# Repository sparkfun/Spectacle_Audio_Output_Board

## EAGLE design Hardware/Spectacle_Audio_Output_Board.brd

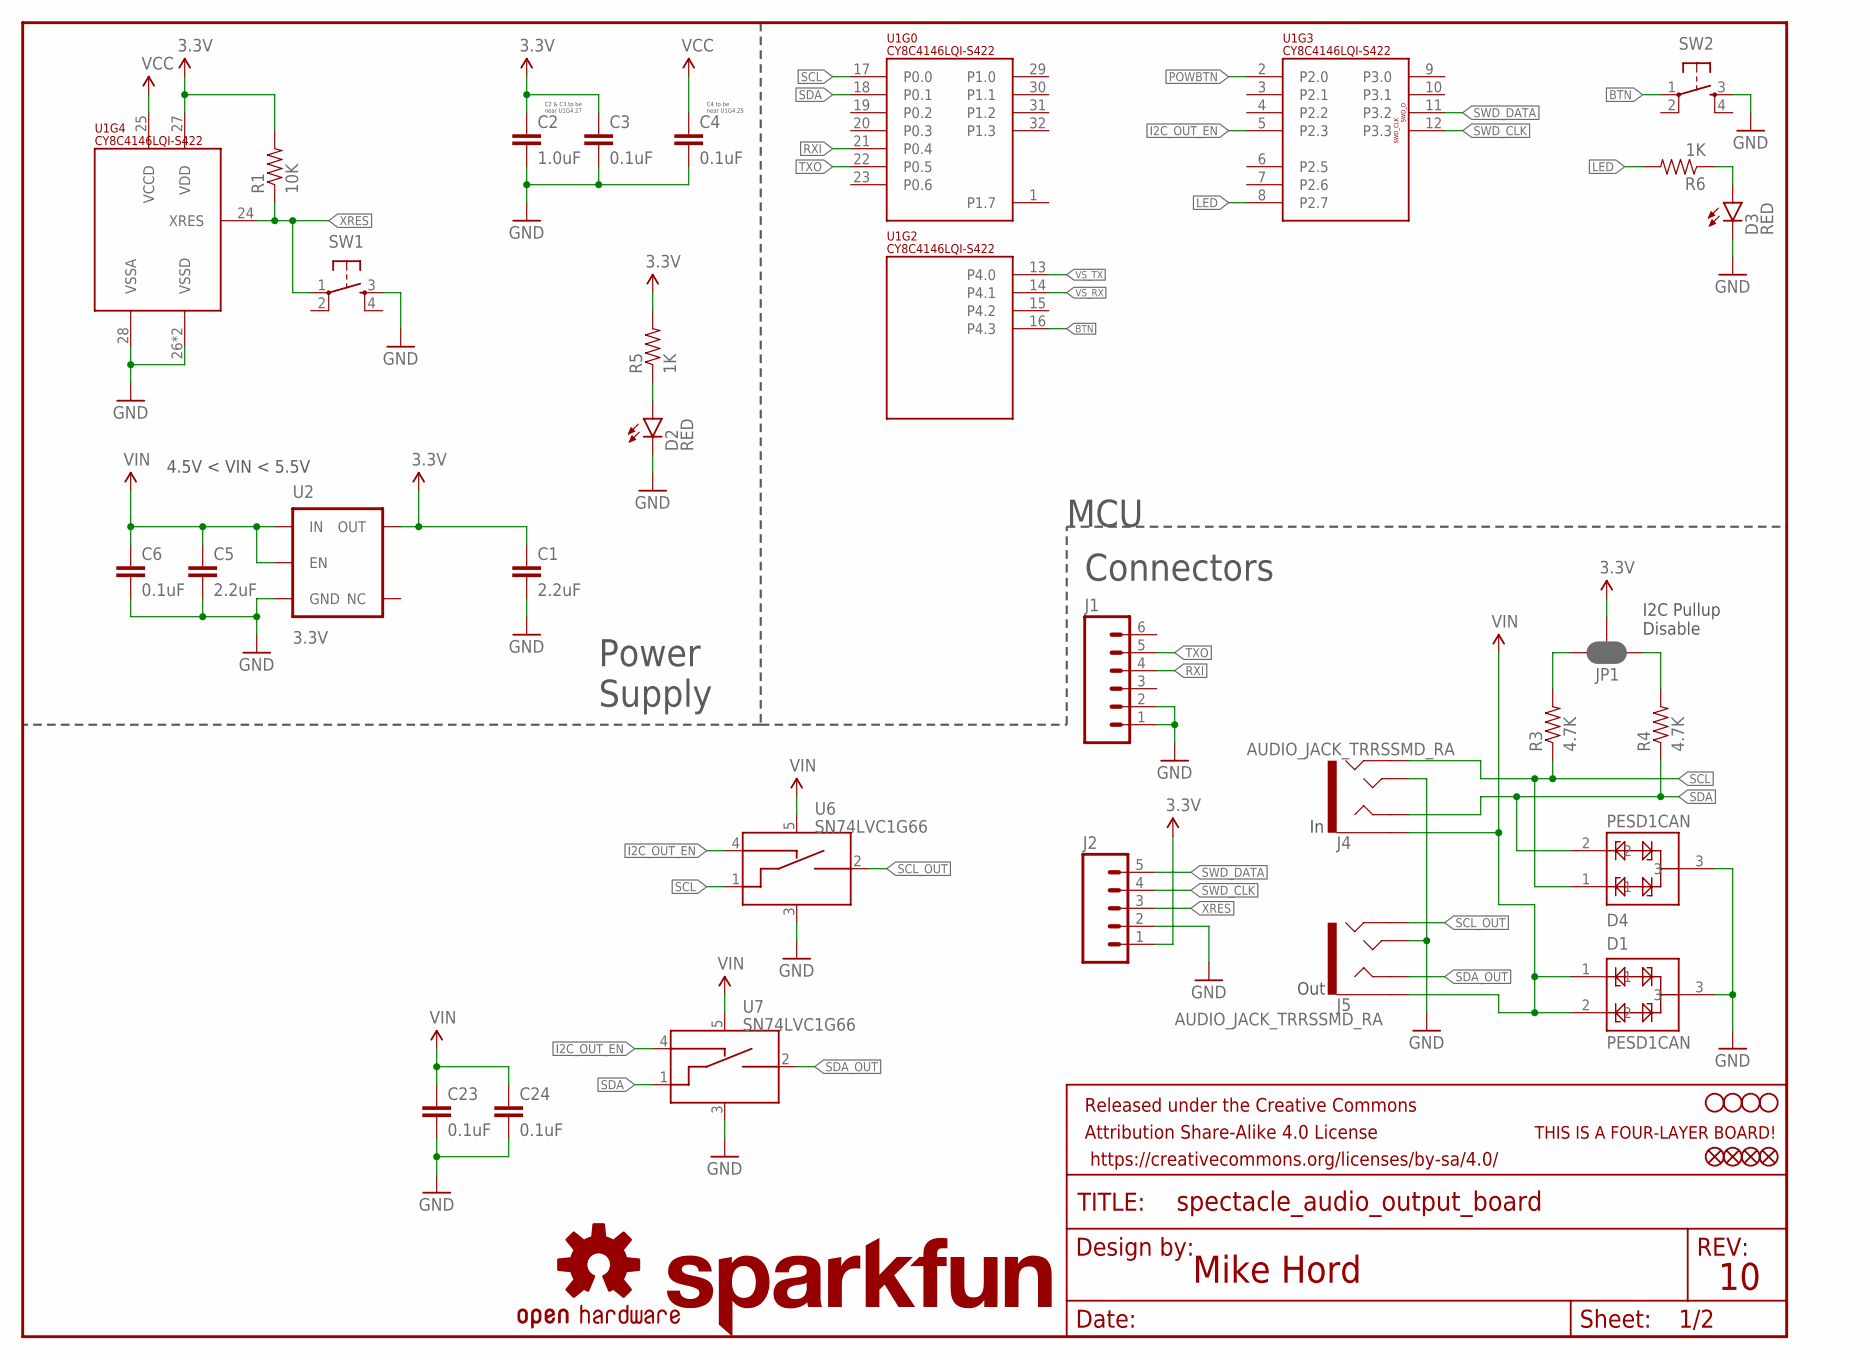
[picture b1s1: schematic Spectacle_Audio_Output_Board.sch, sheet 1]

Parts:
C1, C5: 2.2uF; 0603-CAP
C2: 1.0uF; 0402-CAP
C3, C4, C6, C23, C24: 0.1uF; 0402-CAP
D1, D4: PESD1CAN; SOT23-3
D2, D3: RED; LED-0603
FD5, FD6, FD7, FD8: FIDUCIALUFIDUCIAL; MICRO-FIDUCIAL
FRAME1: FRAME-LETTER; CREATIVE_COMMONS
H1, H2, H3, H4: STAND-OFF
J1: M06NO_SILK_NO_POP; 1X06_NO_SILK
J2: M05NO_SILK; 1X05_NO_SILK
J4, J5: AUDIO_JACK_TRRSSMD_RA; AUDIO_JACK_3.5MM_TRRS_SMD_RA
JP1: JUMPER-PAD-3-NC_BY_PASTE; PAD-JUMPER-3-NC_BY_PASTE_YES_SILK_FULL_BOX
LOGO1: OSHW-LOGOS; OSHW-LOGO-S
LOGO2: SFE_LOGO_NAME.1_INCH; SFE_LOGO_NAME_.1
R1: 10K; 0603-RES
R3, R4: 4.7K; 0603-RES
R5, R6: 1K; 0603-RES
SW1, SW2: SWITCH_SPST_4_PINRECT; TACTILE_SWITCH_SMD_4.6X2.8MM
U1: CY8C4146LQI-S422; QFN-32
U2: 3.3V; SOT23-5
U6, U7: SN74LVC1G66; SOT23-5
U$1: FOUR_LAYER_WARNING

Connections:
3.3V: C1.1, C2.1, C3.1, J2.1, JP1.2, R1.2, R5.2, U1.27 (VDD), U2.5 (OUT); also elsewhere on the board
BTN: SW2.1, U1.16 (P4.3)
GND: C1.2, C2.2, C3.2, C4.2, C5.2, C6.2, C23.2, C24.2, D1.3, D2.C, D3.C, D4.3, J1.1, J1.2, J2.2, J4.TIP, J5.TIP, SW1.3, SW2.3, U1.26 (VSSD), U1.28 (VSSA), U1.EP (VSSD), U2.2 (GND), U6.3 (VSS), U7.3 (VSS); also elsewhere on the board
I2C_OUT_EN: U1.5 (P2.3), U6.4 (CTRL_IN), U7.4 (CTRL_IN)
LED: R6.2, U1.8 (P2.7)
unnamed: JP1.3, R3.2
unnamed: D2.A, R5.1
unnamed: D3.A, R6.1
unnamed: JP1.1, R4.2
POWBTN: U1.2 (P2.0); also elsewhere on the board
RXI: J1.4, U1.21 (P0.4)
SCL: D4.1, J4.RING2, R3.1, U1.17 (P0.0), U6.1 (A_IN)
SCL_OUT: J5.RING2, U6.2 (A_OUT)
SDA: D4.2, J4.RING1, R4.1, U1.18 (P0.1), U7.1 (A_IN)
SDA_OUT: J5.RING1, U7.2 (A_OUT)
SWD_CLK: J2.4, U1.12 (P3.3)
SWD_DATA: J2.5, U1.11 (P3.2)
TXO: J1.5, U1.22 (P0.5)
VCC: C4.1, U1.25 (VCCD)
VIN: C5.1, C6.1, C23.1, C24.1, D1.1, D1.2, J4.EARTH, J5.EARTH, U2.1 (IN), U2.3 (EN), U6.5 (VCC), U7.5 (VCC); also elsewhere on the board
VS_RX: U1.14 (P4.1); also elsewhere on the board
VS_TX: U1.13 (P4.0); also elsewhere on the board
XRES: J2.3, R1.1, SW1.1, U1.24 (XRES)

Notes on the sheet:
C2 & C3 to be near U1G4.27
C4 to be near U1G4.25
Mike Hord
MCU
Connectors
Power Supply
4.5V < VIN < 5.5V
I2C Pullup Disable
Out

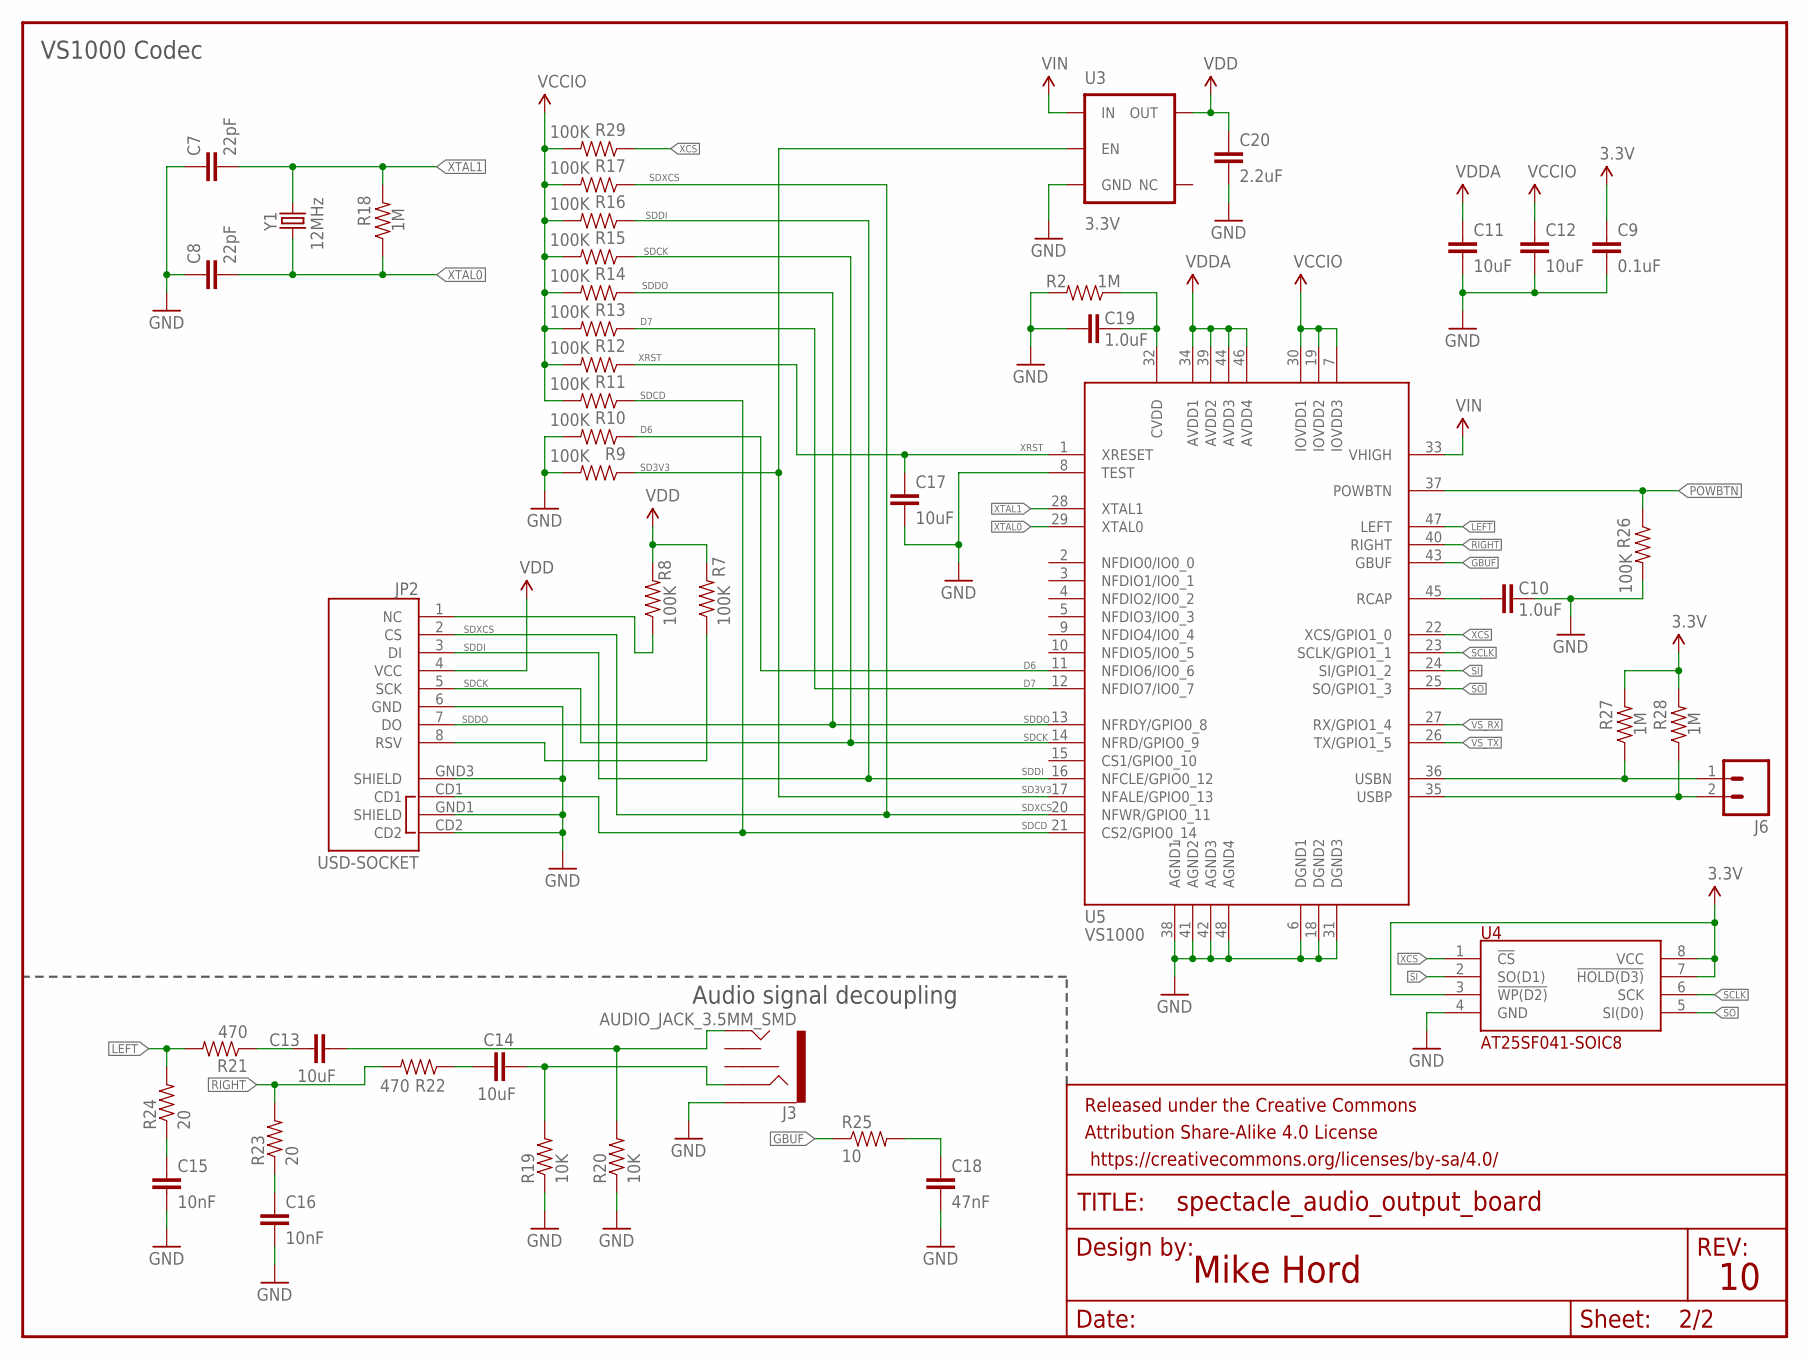
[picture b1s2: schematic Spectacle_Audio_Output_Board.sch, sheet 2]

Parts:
C7, C8: 22pF; 0603-CAP
C9: 0.1uF; 0402-CAP
C10, C19: 1.0uF; 0402-CAP
C11, C12, C13, C14, C17: 10uF; 0603-CAP
C15, C16: 10nF; 0603-CAP
C18: 47nF; 0603-CAP
C20: 2.2uF; 0603-CAP
FRAME2: FRAME-LETTER; CREATIVE_COMMONS
J3: AUDIO_JACK_3.5MM_SMD; AUDIO-JACK-3.5MM-SMD
J6: M021X02_NO_SILK; 1X02_NO_SILK
JP2: USD-SOCKET; MICROSD_1:1
R2, R18, R27, R28: 1M; 0603-RES
R7, R8, R9, R10, R11, R12, R13, R14, R15, R16, R17, R26, R29: 100K; 0402-RES
R19, R20: 10K; 0603-RES
R21, R22: 470; 0603-RES
R23, R24: 20; 0603-RES
R25: 10; 0603-RES
U3: 3.3V; SOT23-5
U4: AT25SF041-SOIC8; SO08
U5: VS1000; LQFP-48
Y1: 12MHz; CRYSTAL-SMD-5X3

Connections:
3.3V: C9.1, R27.2, R28.2, U4.3 (!WP(D2)), U4.7 (!HOLD(D3)), U4.8 (VCC); also elsewhere on the board
D6: R10.1, U5.11 (NFDIO6/IO0_6)
D7: R13.1, U5.12 (NFDIO7/IO0_7)
GBUF: R25.1, U5.43 (GBUF)
GND: C7.1, C8.1, C9.2, C10.2, C11.2, C12.2, C15.2, C16.2, C17.2, C18.2, C19.1, C20.2, J3.SLEEVE, JP2.6 (GND), JP2.CD2, JP2.GND1 (SHIELD), JP2.GND3 (SHIELD), R2.2, R9.2, R10.2, R19.1, R20.1, R26.2, U3.2 (GND), U4.4 (GND), U5.6 (DGND1), U5.8 (TEST), U5.18 (DGND2), U5.31 (DGND3), U5.38 (AGND1), U5.41 (AGND2), U5.42 (AGND3), U5.48 (AGND4); also elsewhere on the board
LEFT: R21.2, R24.2, U5.47 (LEFT)
L_AC: C13.2, J3.TIP, R20.2
unnamed: JP2.1 (NC), R8.1
unnamed: JP2.8 (RSV), R7.1
unnamed: C13.1, R21.1
unnamed: C15.1, R24.1
unnamed: C18.1, R25.2
unnamed: C10.1, U5.45 (RCAP)
unnamed: C19.2, R2.1, U5.32 (CVDD)
unnamed: C14.1, R22.1
unnamed: C16.1, R23.1
POWBTN: R26.1, U5.37 (POWBTN); also elsewhere on the board
RIGHT: R22.2, R23.2, U5.40 (RIGHT)
R_AC: C14.2, J3.RING, R19.2
SCLK: U4.6 (SCK), U5.23 (SCLK/GPIO1_1)
SD3V3: R9.1, U3.3 (EN), U5.17 (NFALE/GPIO0_13)
SDCD: JP2.CD1, R11.1, U5.21 (CS2/GPIO0_14)
SDCK: JP2.5 (SCK), R15.1, U5.14 (NFRD/GPIO0_9)
SDDI: JP2.3 (DI), R16.1, U5.16 (NFCLE/GPIO0_12)
SDDO: JP2.7 (DO), R14.1, U5.13 (NFRDY/GPIO0_8)
SDXCS: JP2.2 (CS), R17.1, U5.20 (NFWR/GPIO0_11)
SI: U4.2 (SO(D1)), U5.24 (SI/GPIO1_2)
SO: U4.5 (SI(D0)), U5.25 (SO/GPIO1_3)
USBN: J6.1, R27.1, U5.36 (USBN)
USBP: J6.2, R28.1, U5.35 (USBP)
VCCIO: C12.1, R11.2, R12.2, R13.2, R14.2, R15.2, R16.2, R17.2, R29.2, U5.7 (IOVDD3), U5.19 (IOVDD2), U5.30 (IOVDD1)
VDD: C20.1, JP2.4 (VCC), R7.2, R8.2, U3.5 (OUT)
VDDA: C11.1, U5.34 (AVDD1), U5.39 (AVDD2), U5.44 (AVDD3), U5.46 (AVDD4)
VIN: U3.1 (IN), U5.33 (VHIGH); also elsewhere on the board
VS_RX: U5.27 (RX/GPIO1_4); also elsewhere on the board
VS_TX: U5.26 (TX/GPIO1_5); also elsewhere on the board
XCS: R29.1, U4.1 (!CS), U5.22 (XCS/GPIO1_0)
XRST: C17.1, R12.1, U5.1 (XRESET)
XTAL0: C8.2, R18.1, U5.29 (XTAL0), Y1.1
XTAL1: C7.2, R18.2, U5.28 (XTAL1), Y1.3 (2)

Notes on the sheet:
Audio signal decoupling
VS1000 Codec
Mike Hord

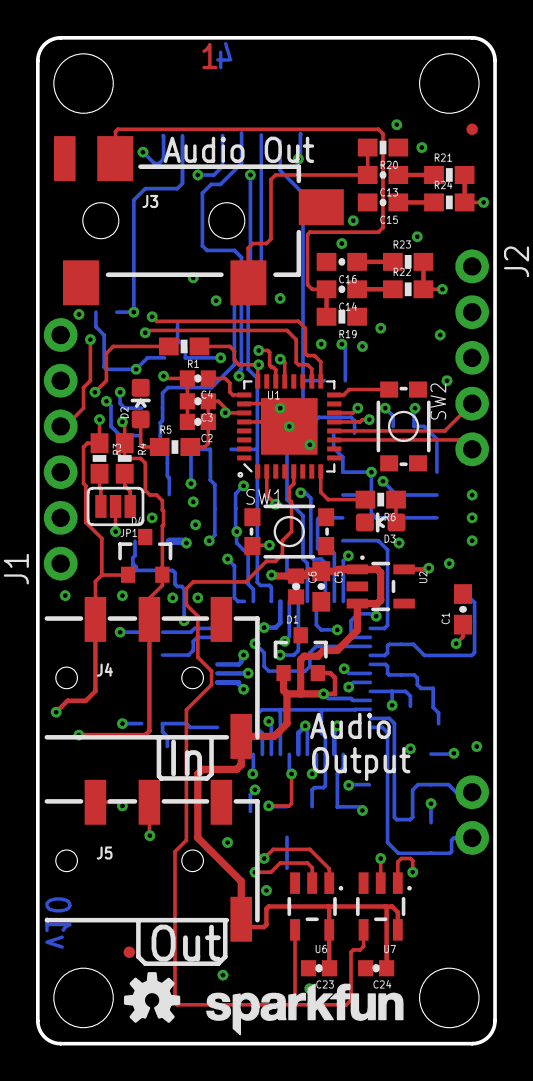
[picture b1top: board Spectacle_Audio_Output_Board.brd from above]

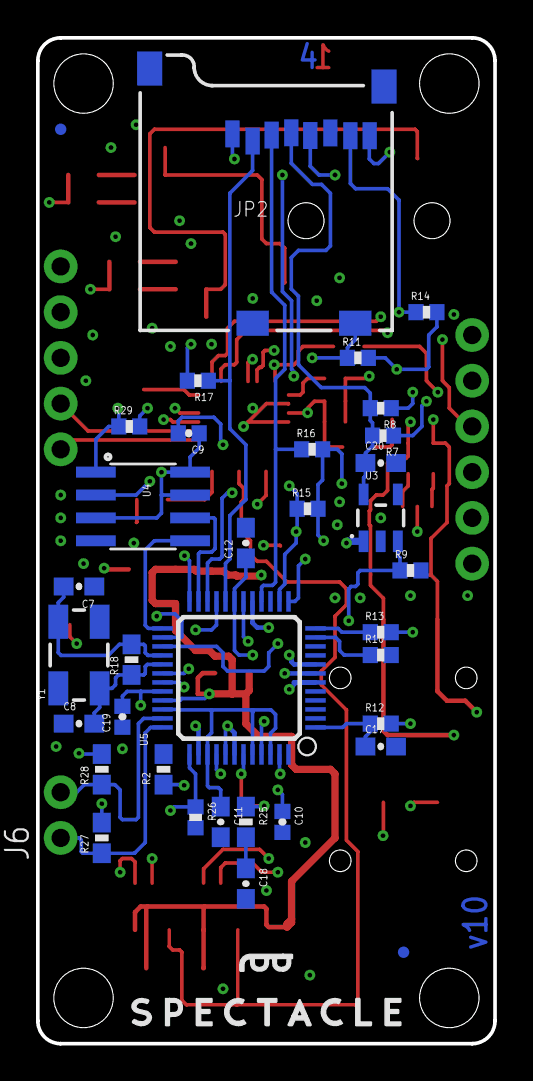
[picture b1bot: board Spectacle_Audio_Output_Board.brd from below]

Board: 4 copper layers, 25.4 x 55.9 mm, 86 parts (36 on the bottom side), 57 nets.

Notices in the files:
Firmware/VS1000AudioModule/usbmass.c:
Copyright 2008-2011 VLSI Solution Oy. Absolutely no warranty.
parts and their libraries:
SparkFun-Aesthetics: Licensing: Creative Commons ShareAlike 4.0 International - https://creativecommons.org/licenses/by-sa/4.0
SparkFun-Aesthetics: Released under the Creative Commons Attribution Share-Alike 4.0 License
SparkFun-Aesthetics: https://creativecommons.org/licenses/by-sa/4.0
